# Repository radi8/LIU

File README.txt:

# LIU
Line Interface Unit for a repeater Linking Repeater with equalizer and delay

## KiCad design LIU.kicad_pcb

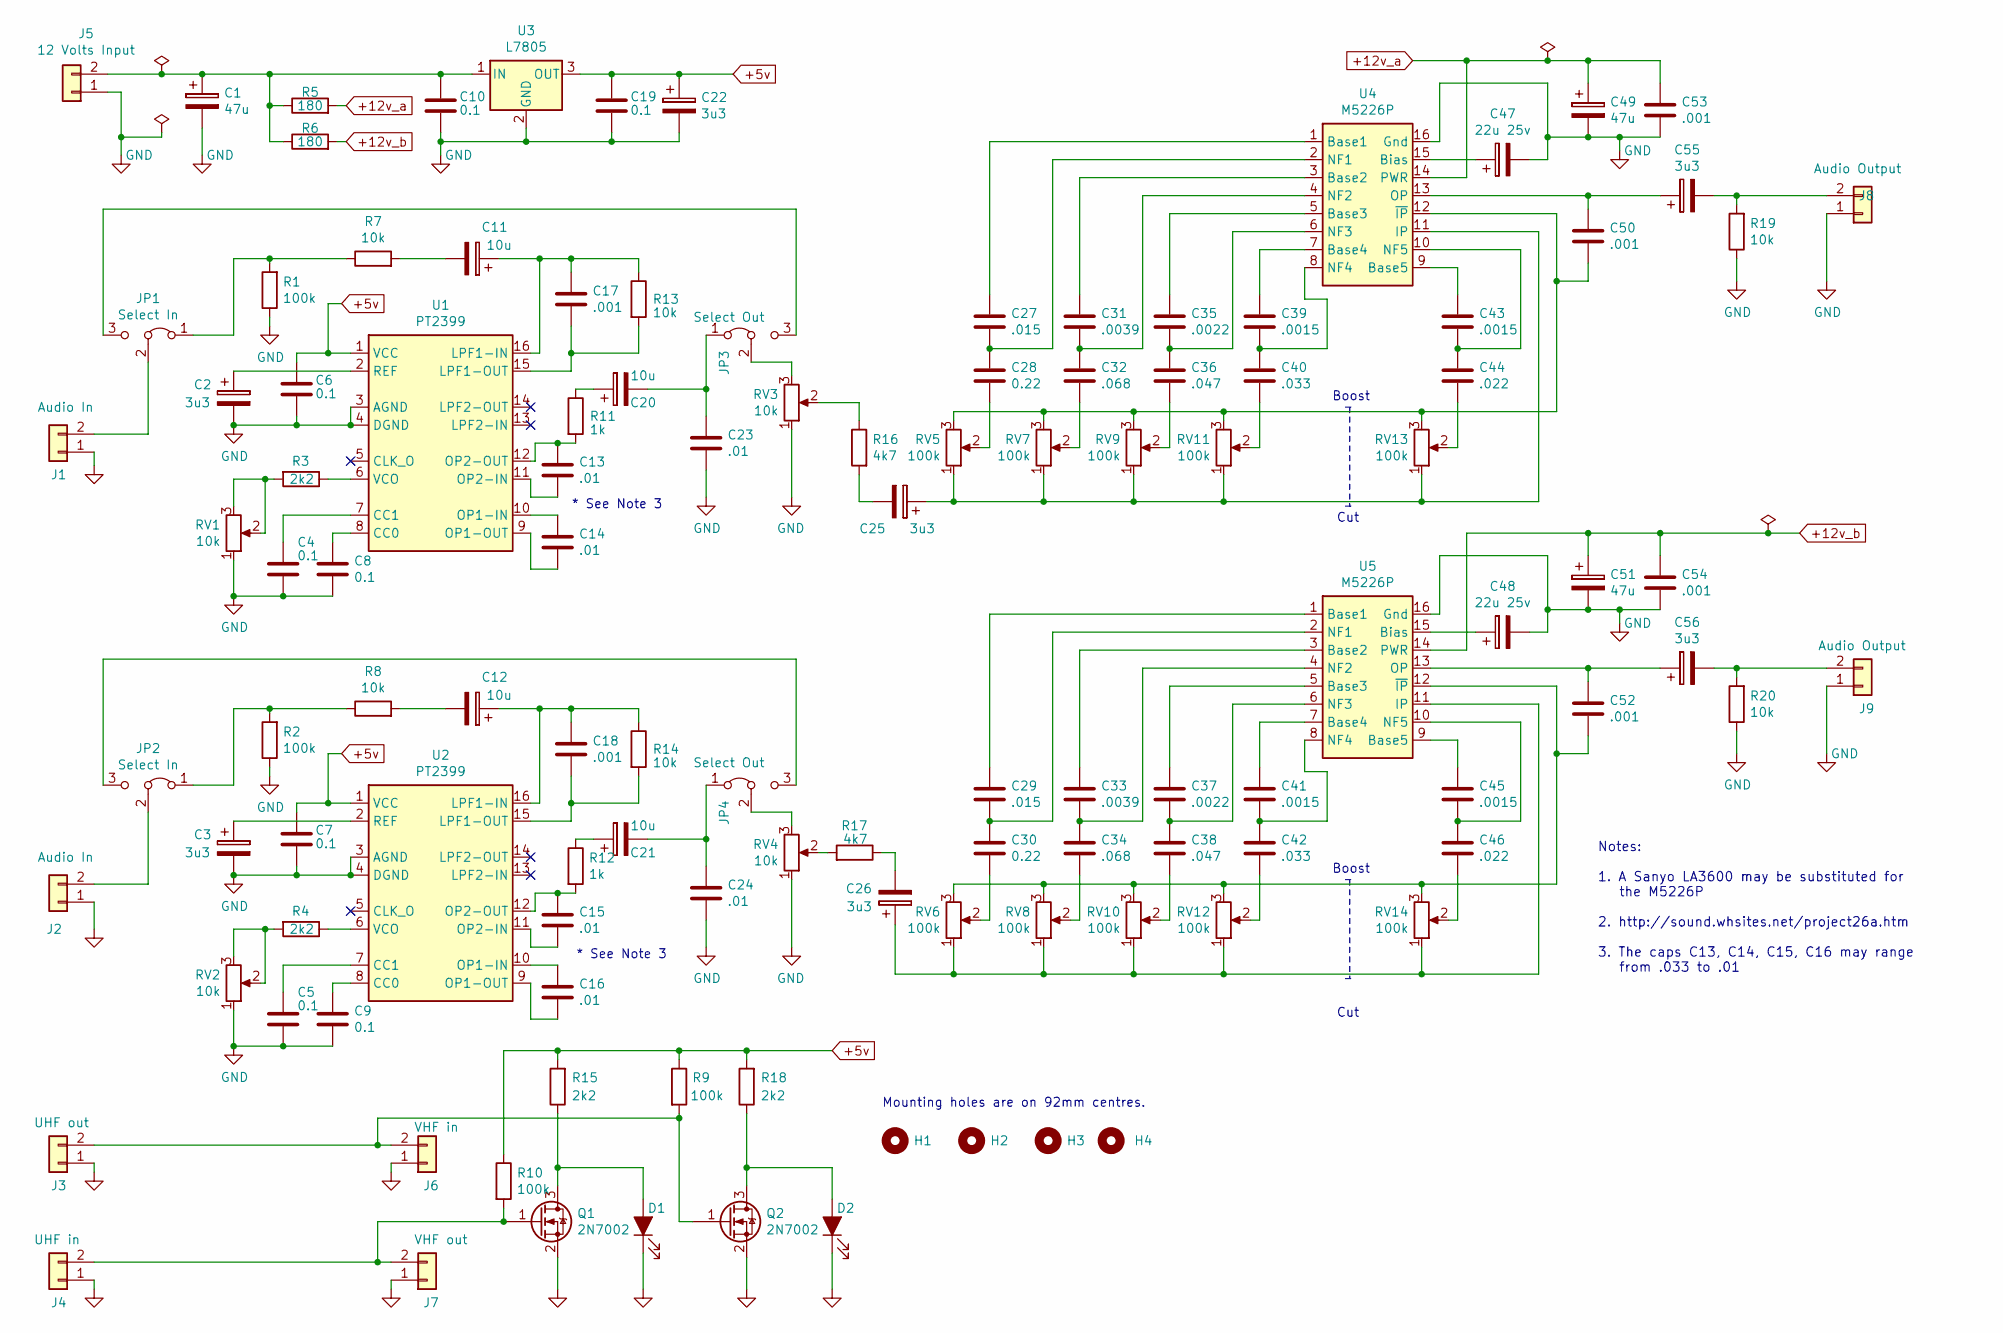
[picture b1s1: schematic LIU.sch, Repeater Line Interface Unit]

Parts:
C1, C49, C51: 47u; CP_Elec_6.3x5.2
C2, C3, C22, C25, C26, C55, C56: 3u3; CP_Elec_5x5.3
C4, C5, C6, C7, C8, C9, C10, C19: 0.1; C_1206_3216Metric_Pad1.42x1.75mm_HandSolder
C11, C12, C20, C21: 10u; CP_Elec_5x5.3
C13, C14, C15, C16, C23, C24: .01; C_1206_3216Metric_Pad1.42x1.75mm_HandSolder
C17, C18, C50, C52, C53, C54: .001; C_1206_3216Metric_Pad1.42x1.75mm_HandSolder
C27, C29: .015; C_1206_3216Metric_Pad1.42x1.75mm_HandSolder
C28, C30: 0.22; C_1206_3216Metric_Pad1.42x1.75mm_HandSolder
C31, C33: .0039; C_1206_3216Metric_Pad1.42x1.75mm_HandSolder
C32, C34: .068; C_1206_3216Metric_Pad1.42x1.75mm_HandSolder
C35, C37: .0022; C_1206_3216Metric_Pad1.42x1.75mm_HandSolder
C36, C38: .047; C_1206_3216Metric_Pad1.42x1.75mm_HandSolder
C39, C41, C43, C45: .0015; C_1206_3216Metric_Pad1.42x1.75mm_HandSolder
C40, C42: .033; C_1206_3216Metric_Pad1.42x1.75mm_HandSolder
C44, C46: .022; C_1206_3216Metric_Pad1.42x1.75mm_HandSolder
C47, C48: 22u 25v; CP_Elec_5x5.3
D1, D2: LED_ALT; LED_1206_3216Metric_Pad1.42x1.75mm_HandSolder
H1, H2, H3, H4: MountingHole; MountingHole_3.2mm_M3
J1, J2: Audio In; PinHeader_1x02_P2.54mm_Vertical
J3: UHF out; PinHeader_1x02_P2.54mm_Vertical
J4: UHF in; PinHeader_1x02_P2.54mm_Vertical
J5: 12 Volts Input; PinHeader_1x02_P2.54mm_Vertical
J6: VHF in; PinHeader_1x02_P2.54mm_Vertical
J7: VHF out; PinHeader_1x02_P2.54mm_Vertical
J8, J9: Audio Output; PinHeader_1x02_P2.54mm_Vertical
JP1, JP2: Select In; PinHeader_1x03_P2.54mm_Vertical
JP3, JP4: Select Out; PinHeader_1x03_P2.54mm_Vertical
Q1, Q2: 2N7002; SOT-23_Handsoldering
R1, R2, R9, R10: 100k; R_1206_3216Metric_Pad1.42x1.75mm_HandSolder
R3, R4, R15, R18: 2k2; R_1206_3216Metric_Pad1.42x1.75mm_HandSolder
R5, R6: 180; R_1206_3216Metric_Pad1.42x1.75mm_HandSolder
R7, R8, R13, R14, R19, R20: 10k; R_1206_3216Metric_Pad1.42x1.75mm_HandSolder
R11, R12: 1k; R_1206_3216Metric_Pad1.42x1.75mm_HandSolder
R16, R17: 4k7; R_1206_3216Metric_Pad1.42x1.75mm_HandSolder
RV1, RV2, RV3, RV4: 10k; Potentiometer_Bourns_3386P_Vertical
RV5, RV6, RV7, RV8, RV9, RV10, RV11, RV12, RV13, RV14: 100k; Potentiometer_Bourns_3386P_Vertical
U1, U2: PT2399; DIP-16_W7.62mm_LongPads
U3: L7805; TO-220-3_Horizontal_TabDown
U4, U5: M5226P; DIP-16_W7.62mm_LongPads

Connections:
+5v: C6.1, C7.1, C19.1, C22.1, R9.1, R10.1, R15.2, R18.2, U1.1 (VCC), U2.1 (VCC), U3.3 (OUT)
+12v_a: C49.1, C53.1, R5.2, U4.14 (PWR)
+12v_b: C51.1, C54.1, R6.2, U5.14 (PWR)
GND: C1.2, C2.2, C3.2, C4.2, C5.2, C6.2, C7.2, C8.2, C9.2, C10.2, C19.2, C22.2, C23.2, C24.2, C47.2, C48.2, C49.2, C51.2, C53.2, C54.2, D1.1 (K), D2.1 (K), J1.1, J2.1, J3.1, J4.1, J5.1, J6.1, J7.1, J8.1, J9.1, Q1.2 (S), Q2.2 (S), R1.1, R2.1, R19.1, R20.1, RV1.1, RV2.1, RV3.1, RV4.1, U1.3 (AGND), U1.4 (DGND), U2.3 (AGND), U2.4 (DGND), U3.2 (GND), U4.16 (Gnd), U5.16 (Gnd)
unnamed: C1.1, C10.1, J5.2, R5.1, R6.1, U3.1 (IN)
unnamed: C2.1, U1.2 (REF)
unnamed: C3.1, U2.2 (REF)
unnamed: C4.1, U1.7 (CC1)
unnamed: C5.1, U2.7 (CC1)
unnamed: C8.1, U1.8 (CC0)
unnamed: C9.1, U2.8 (CC0)
unnamed: C11.1, C17.1, R13.1, U1.16 (LPF1-IN)
unnamed: C11.2, R7.2
unnamed: C12.1, C18.1, R14.1, U2.16 (LPF1-IN)
unnamed: C12.2, R8.2
unnamed: C13.1, R11.2, U1.12 (OP2-OUT)
unnamed: C13.2, U1.11 (OP2-IN)
unnamed: C14.1, U1.10 (OP1-IN)
unnamed: C14.2, U1.9 (OP1-OUT)
unnamed: C15.1, R12.2, U2.12 (OP2-OUT)
unnamed: C15.2, U2.11 (OP2-IN)
unnamed: C16.1, U2.10 (OP1-IN)
unnamed: C16.2, U2.9 (OP1-OUT)
unnamed: C17.2, R13.2, U1.15 (LPF1-OUT)
unnamed: C18.2, R14.2, U2.15 (LPF1-OUT)
unnamed: C20.1, R11.1
unnamed: C20.2, C23.1, JP3.1 (A)
unnamed: C21.1, R12.1
unnamed: C21.2, C24.1, JP4.1 (A)
unnamed: C25.1, RV5.1, RV7.1, RV9.1, RV11.1, RV13.1, U4.11 (IP)
unnamed: C25.2, R16.2
unnamed: C26.1, RV6.1, RV8.1, RV10.1, RV12.1, RV14.1, U5.11 (IP)
unnamed: C26.2, R17.1
unnamed: C27.1, U4.1 (Base1)
unnamed: C27.2, C28.1, U4.2 (NF1)
unnamed: C28.2, RV5.2
unnamed: C29.1, U5.1 (Base1)
unnamed: C29.2, C30.1, U5.2 (NF1)
unnamed: C30.2, RV6.2
unnamed: C31.1, U4.3 (Base2)
unnamed: C31.2, C32.1, U4.4 (NF2)
unnamed: C32.2, RV7.2
unnamed: C33.1, U5.3 (Base2)
unnamed: C33.2, C34.1, U5.4 (NF2)
unnamed: C34.2, RV8.2
unnamed: C35.1, U4.5 (Base3)
unnamed: C35.2, C36.1, U4.6 (NF3)
unnamed: C36.2, RV9.2
unnamed: C37.1, U5.5 (Base3)
unnamed: C37.2, C38.1, U5.6 (NF3)
unnamed: C38.2, RV10.2
unnamed: C39.1, U4.7 (Base4)
unnamed: C39.2, C40.1, U4.8 (NF4)
unnamed: C40.2, RV11.2
unnamed: C41.1, U5.7 (Base4)
unnamed: C41.2, C42.1, U5.8 (NF4)
unnamed: C42.2, RV12.2
unnamed: C43.1, U4.9 (Base5)
unnamed: C43.2, C44.1, U4.10 (NF5)
unnamed: C44.2, RV13.2
unnamed: C45.1, U5.9 (Base5)
unnamed: C45.2, C46.1, U5.10 (NF5)
unnamed: C46.2, RV14.2
unnamed: C47.1, U4.15 (Bias)
unnamed: C48.1, U5.15 (Bias)
unnamed: C50.1, C55.1, U4.13 (OP)
unnamed: C50.2, RV5.3, RV7.3, RV9.3, RV11.3, RV13.3, U4.12 (~IP)
unnamed: C52.1, C56.1, U5.13 (OP)
unnamed: C52.2, RV6.3, RV8.3, RV10.3, RV12.3, RV14.3, U5.12 (~IP)
unnamed: C55.2, J8.2, R19.2
unnamed: C56.2, J9.2, R20.2
unnamed: D1.2 (A), Q1.3 (D), R15.1
unnamed: D2.2 (A), Q2.3 (D), R18.1
unnamed: J1.2, JP1.2 (C)
unnamed: J2.2, JP2.2 (C)
unnamed: J3.2, J6.2, Q2.1 (G), R9.2
unnamed: J4.2, J7.2, Q1.1 (G), R10.2
unnamed: JP1.1 (A), R1.2, R7.1
unnamed: JP1.3 (B), JP3.3 (B)
unnamed: JP2.1 (A), R2.2, R8.1
unnamed: JP2.3 (B), JP4.3 (B)
unnamed: JP3.2 (C), RV3.3
unnamed: JP4.2 (C), RV4.3
unnamed: R3.1, U1.6 (VCO)
unnamed: R3.2, RV1.2, RV1.3
unnamed: R4.1, U2.6 (VCO)
unnamed: R4.2, RV2.2, RV2.3
unnamed: R16.1, RV3.2
unnamed: R17.2, RV4.2

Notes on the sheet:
Boost
Cut
Notes: 1. A Sanyo LA3600 may be substituted for the M5226P 2. http://sound.whsites.net/project26a.htm 3. The caps C13, C14, C15, C16 may range from .033 to .01
* See Note 3
Mounting holes are on 92mm centres.

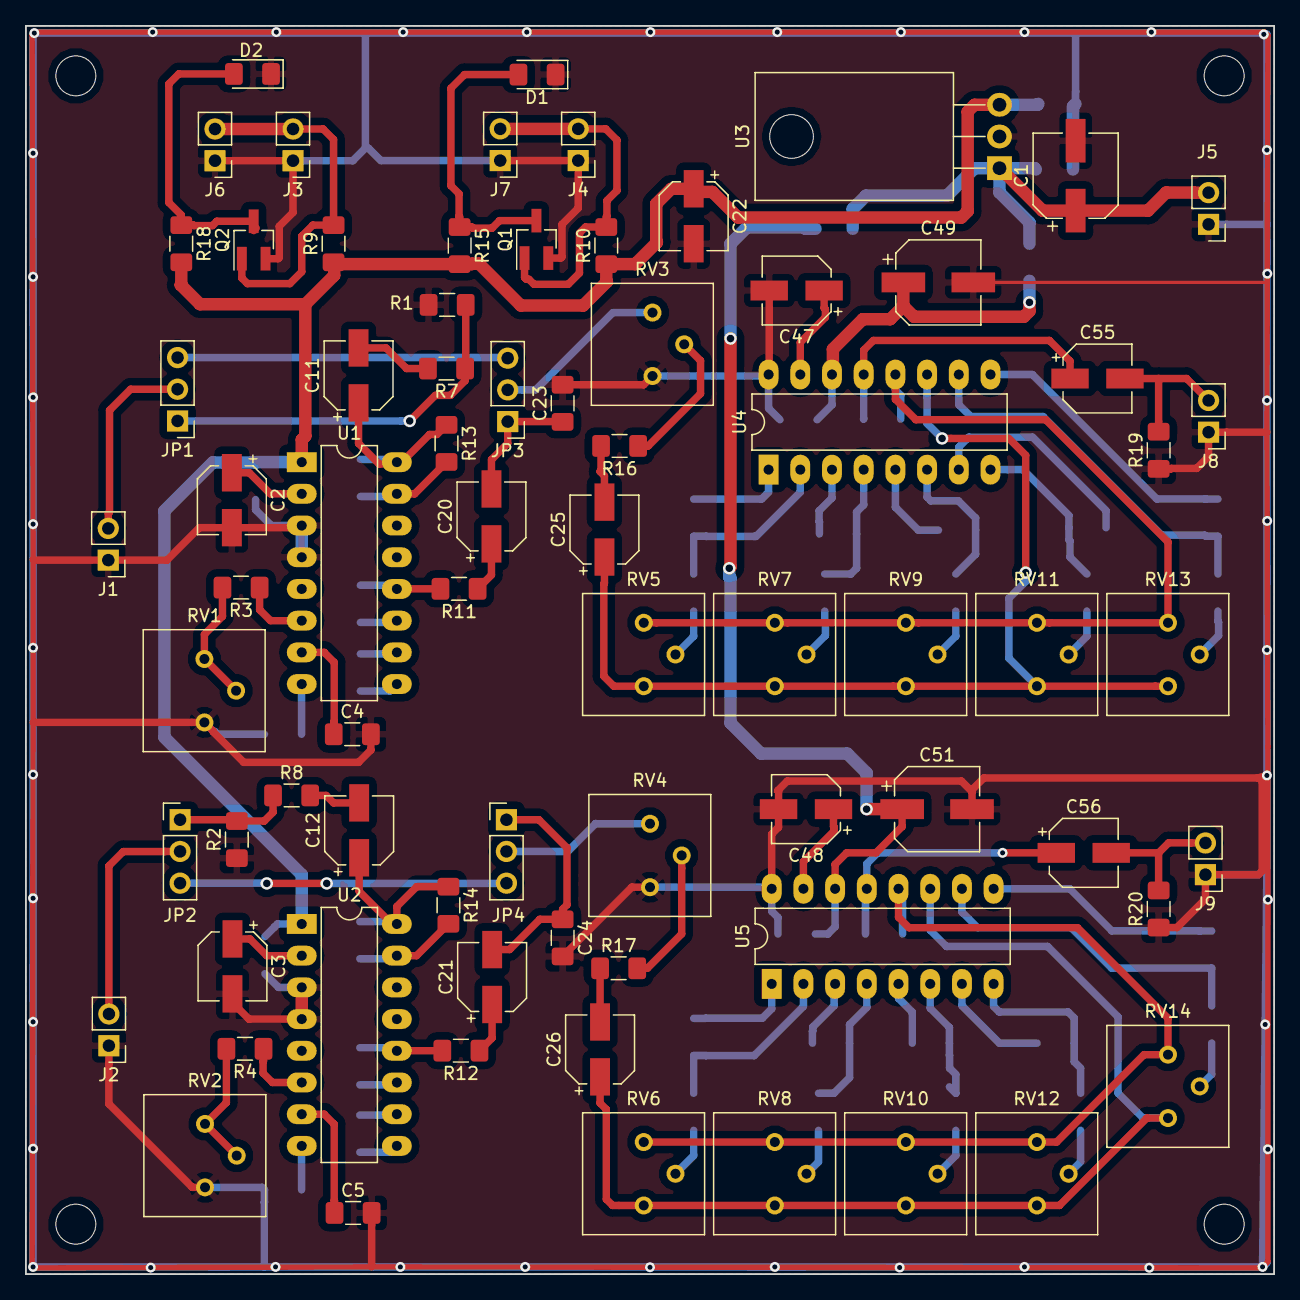
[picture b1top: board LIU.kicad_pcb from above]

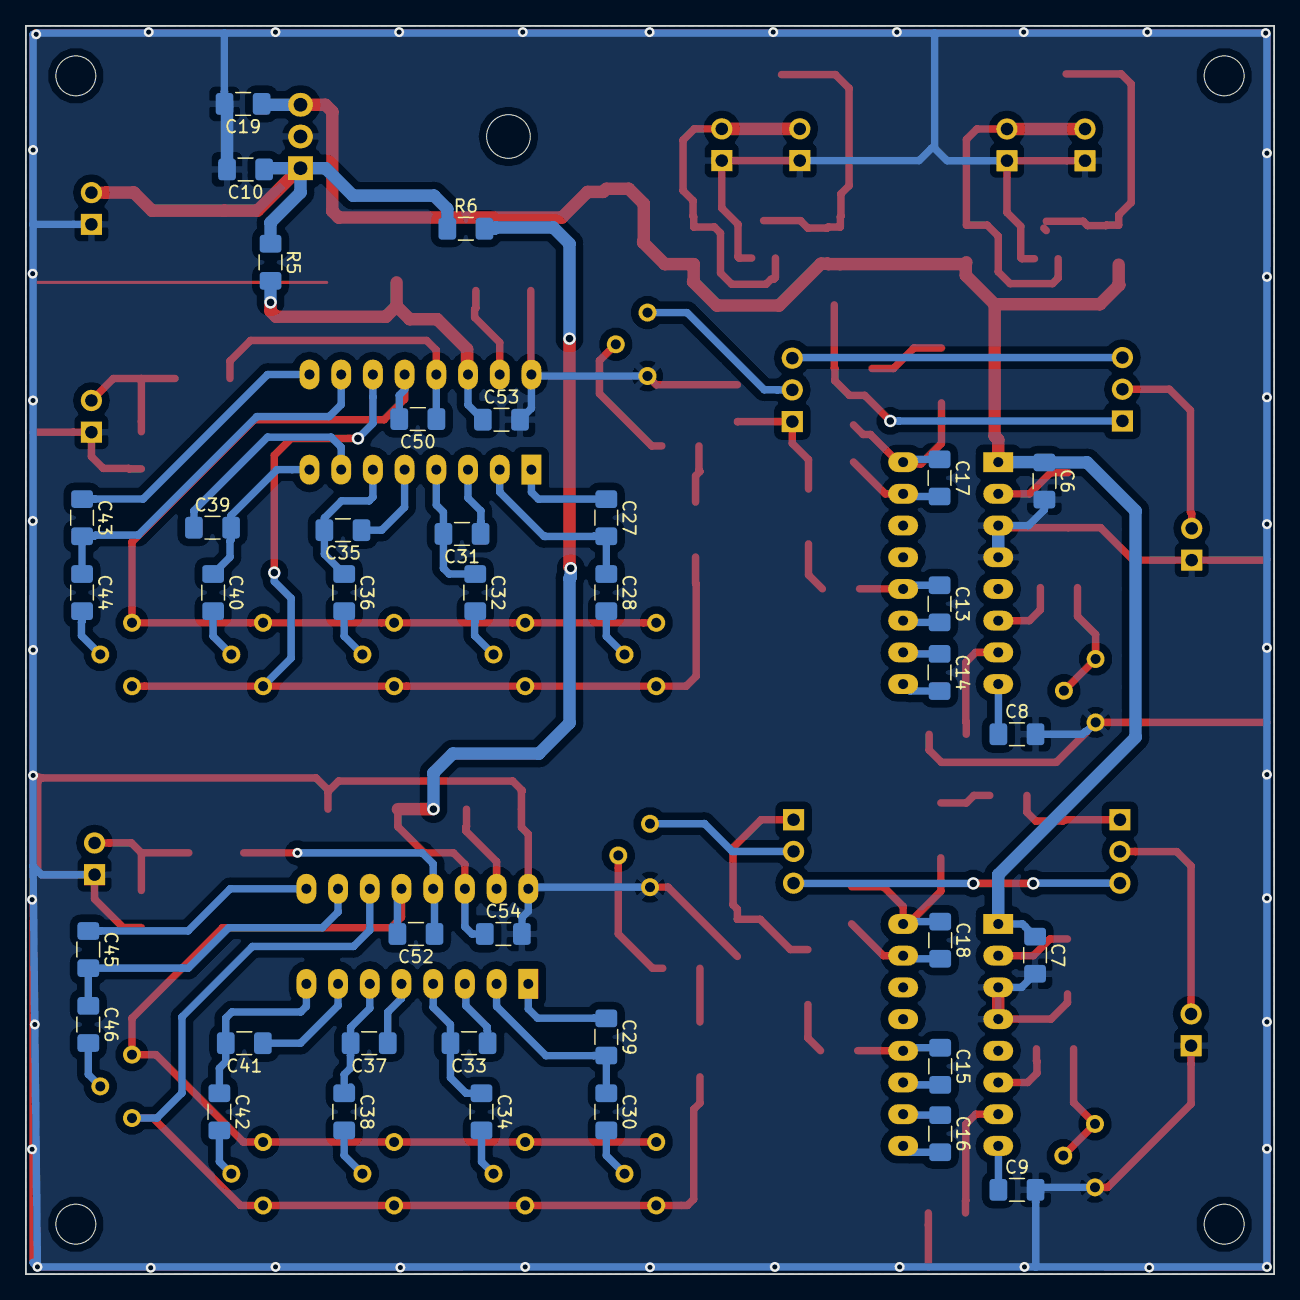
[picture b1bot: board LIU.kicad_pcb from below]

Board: 2 copper layers, 100.0 x 100.0 mm, 116 parts (38 on the bottom side), 89 nets.

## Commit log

2018-10-13 Created the schematic drawing
2018-10-14 Created space in schematic for signaling wiring
2018-10-24 Schematic finalised & layout commenced
2018-10-24 Updated libraries to latest version
2018-10-24 Further layout work
2018-10-25 All components on the board
2018-10-25 Synchronised libraries on both machines
2018-10-25 Further PCB layout
2018-10-26 Project completed
2018-10-26 Added BOM information
